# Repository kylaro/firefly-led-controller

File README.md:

# firefly-led-controller
PCB for the FireFly LED Controller by kylarLEDs

https://imgur.com/a/bOtsNqd

## Hardware
    The sensors on the board are:
        1. Microphone  -> for sound reactive LEDs
        2. Potentiometer  -> for brightness control
        3. Rotary encoder  -> for color/hue control
        4. Rotary encoder button  -> for changing patterns

    The outputs from the board are:
        1. 2 x WS2812B LED output pins 
            a. Each pin has 2 output pads, one on front and one on back
            b. Each pin has a 0.1 inch header port
        2. 2 x USBC 5V power up to 3A

    The input to the boards are:
        1. Pico programming micro usb port (not meant for power)
        2. 1 x USBC 5V power up to 3A

## Notes
Necessary improvements:
  * Support for 4 pin ws2812b strips, and APA102, 4 outputs
  * More testing capability for the microphone, and maybe other components
*     -> maybe bottom of board row of headers that another board with a pi can plug into, or row of pads on bottom
*     -> Or pad groups on the bottom, like this to that type things... every connection could be represented
*     -> ex. MIC GND <-> GND ... ENC_A <-> GP22 ..., anything that contributes functionality :) 
  * 4 LED outputs
  * Header pins offset

Possibile Improvements to make:
    *WIRELESS:
    *Add ESP32 S2 ($2) with PCB antenna, may need a 3.3V regulator unless the 3.3V port can handle it
  * Add a power MOSFET to turn on / off the power to LEDs
  * Have power pads for screw down crimped ring terminals?
  * Have a hole on the board to weave the LED wire through to add mechanical stability to solder connections
  * Support for 12V on board? (5v regulator, 5v dataline, but 12v power)
  * Support for automatically detecting strip length based on current drawn by strip (either "off" current or turning 1 on at a time, need ammeter)
  * Support for battery charging
  * Support for DMX LEDs input/output
  * Add more sensors, like motion sensor for human presence detection. Temperature/accelerometer/humidity/gyro...
  * Add silabs MCU for mesh networking
  * Stop using Pico board, use the RP2040 + pico schematic so we aren't soldering a board onto a board!

Notes:
  * USB C holes should be more exact so it fits better

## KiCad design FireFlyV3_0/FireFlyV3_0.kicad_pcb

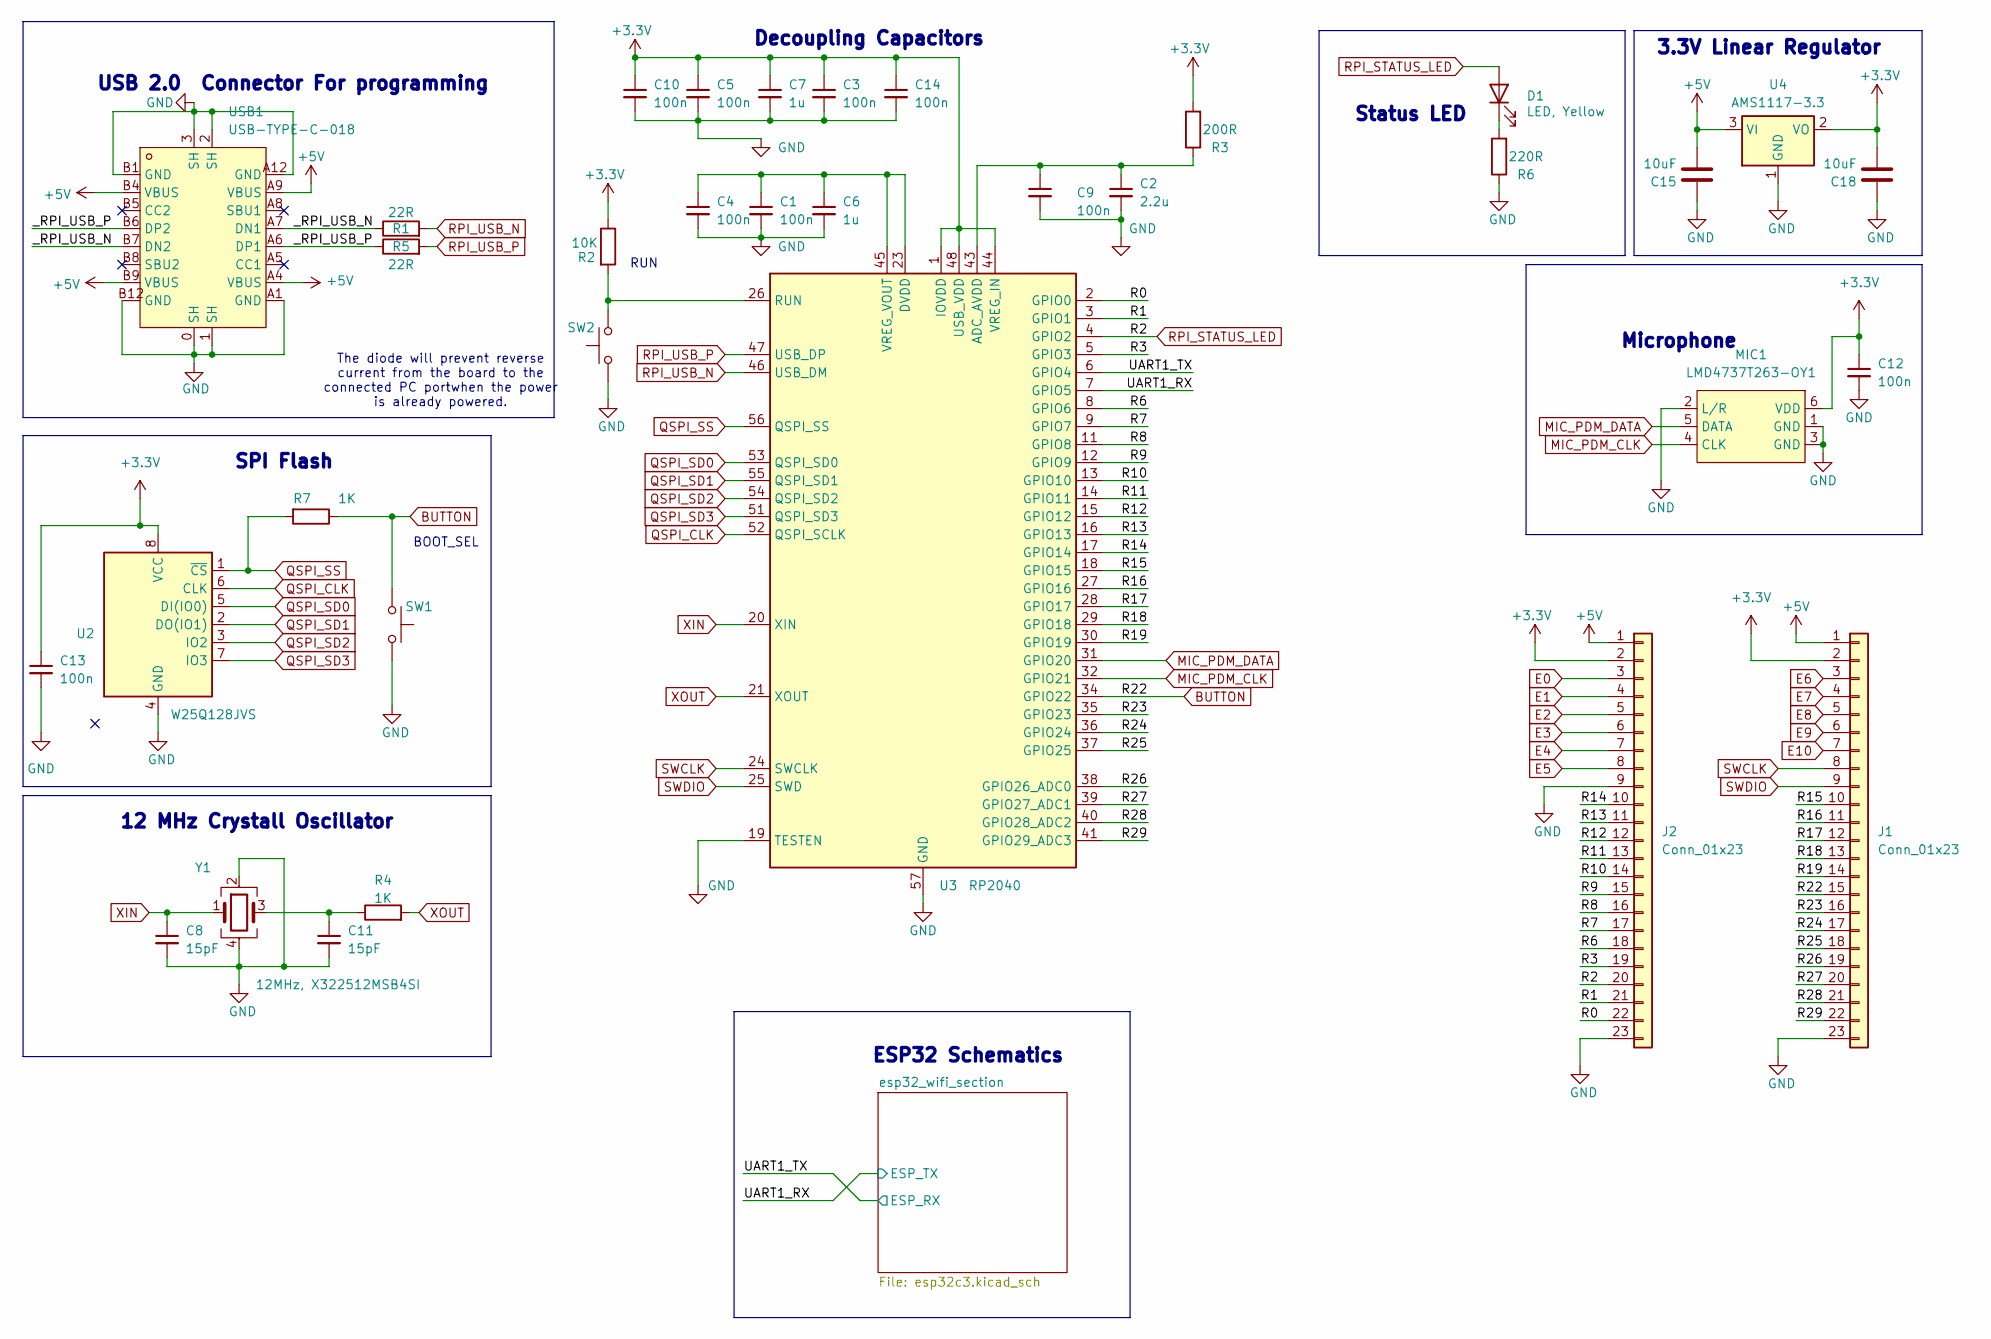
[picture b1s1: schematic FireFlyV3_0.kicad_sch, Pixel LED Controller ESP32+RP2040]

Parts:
C1, C3, C4, C5, C9, C10, C12, C13, C14: 100n; C_0402_1005Metric; LCSC Part C1525
C2: 2.2u; C_0402_1005Metric; LCSC Part C12530
C6, C7: 1u; C_0402_1005Metric; LCSC Part C52923
C8, C11: 15pF; C_0402_1005Metric; LCSC Part C1548
C15, C18: 10uF; C_0603_1608Metric; LCSC Part C19702
D1: LED, Yellow; LED_0603_1608Metric; LCSC Part C72038
J1, J2: Conn_01x23; PinHeader_1x23_P2.54mm_Vertical
MIC1: LMD4737T263-OY1; LGA-6_L4.7-W3.8-P1.65_LMD4737T; LCSC Part C5373239
R1, R5: 22R; R_0402_1005Metric; LCSC Part C25092
R2: 10K; R_0402_1005Metric; LCSC Part C25744
R3: 200R; R_0402_1005Metric; LCSC Part C25087
R4, R7: 1K; R_0402_1005Metric; LCSC Part C11702
R6: 220R; R_0402_1005Metric; LCSC Part C25091
SW1, SW2: BTN; SW_SPST_TL3342; LCSC Part C318884
U2: W25Q128JVS; SOIC-8_5.275x5.275mm_P1.27mm; LCSC Part C97521
U3: RP2040; QFN-56-1EP_7x7mm_P0.4mm_EP3.2x3.2mm; LCSC Part C2040
U4: AMS1117-3.3; SOT-223-3_TabPin2; LCSC Part C6186
USB1: USB-TYPE-C-018; USB-C_SMD-TYPE-C-31-M-12; LCSC Part C2927038
Y1: 12MHz, X322512MSB4SI; Crystal_SMD_3225-4Pin_3.2x2.5mm; LCSC Part C9002

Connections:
+3.3V: C3.1, C5.1, C7.1, C10.1, C12.1, C13.1, C14.1, C18.1, J1.2, J2.2, MIC1.6 (VDD), R2.1, R3.2, U2.8 (VCC), U3.1 (IOVDD), U3.10 (IOVDD), U3.22 (IOVDD), U3.33 (IOVDD), U3.42 (IOVDD), U3.44 (VREG_IN), U3.48 (USB_VDD), U3.49 (IOVDD), U4.2 (VO); also elsewhere on the board
+5V: C15.1, J1.1, J2.1, U4.3 (VI), USB1.A4 (VBUS), USB1.A9 (VBUS), USB1.B4 (VBUS), USB1.B9 (VBUS); also elsewhere on the board
/R0: J2.22, U3.2 (GPIO0)
/R1: J2.21, U3.3 (GPIO1)
/R3: J2.19, U3.5 (GPIO3)
/R6: J2.18, U3.8 (GPIO6)
/R7: J2.17, U3.9 (GPIO7)
/R8: J2.16, U3.11 (GPIO8)
/R9: J2.15, U3.12 (GPIO9)
/R10: J2.14, U3.13 (GPIO10)
/R11: J2.13, U3.14 (GPIO11)
/R12: J2.12, U3.15 (GPIO12)
/R13: J2.11, U3.16 (GPIO13)
/R14: J2.10, U3.17 (GPIO14)
/R15: J1.10, U3.18 (GPIO15)
/R16: J1.11, U3.27 (GPIO16)
/R17: J1.12, U3.28 (GPIO17)
/R18: J1.13, U3.29 (GPIO18)
/R19: J1.14, U3.30 (GPIO19)
/R23: J1.16, U3.35 (GPIO23)
/R24: J1.17, U3.36 (GPIO24)
/R25: J1.18, U3.37 (GPIO25)
/R26: J1.19, U3.38 (GPIO26_ADC0)
/R27: J1.20, U3.39 (GPIO27_ADC1)
/R28: J1.21, U3.40 (GPIO28_ADC2)
/R29: J1.22, U3.41 (GPIO29_ADC3)
/UART1_RX: U3.7 (GPIO5); also elsewhere on the board
/UART1_TX: U3.6 (GPIO4); also elsewhere on the board
/_RPI_USB_N: R1.1, USB1.A7 (DN1), USB1.B7 (DN2)
/_RPI_USB_P: R5.1, USB1.A6 (DP1), USB1.B6 (DP2)
BUTTON: J1.15, R7.1, SW1.1, U3.34 (GPIO22)
E0: J2.3; also elsewhere on the board
E1: J2.4; also elsewhere on the board
E2: J2.5; also elsewhere on the board
E3: J2.6; also elsewhere on the board
E4: J2.7; also elsewhere on the board
E5: J2.8; also elsewhere on the board
E6: J1.3; also elsewhere on the board
E7: J1.4; also elsewhere on the board
E8: J1.5; also elsewhere on the board
E9: J1.6; also elsewhere on the board
E10: J1.7; also elsewhere on the board
GND: C1.2, C2.2, C3.2, C4.2, C5.2, C6.2, C7.2, C8.2, C9.2, C10.2, C11.2, C12.2, C13.2, C14.2, C15.2, C18.2, J1.23, J2.9, J2.23, MIC1.1 (GND), MIC1.2 (L/R), MIC1.3 (GND), R6.1, SW1.2, SW2.2, U2.4 (GND), U3.19 (TESTEN), U3.57 (GND), U4.1 (GND), USB1.0 (SH), USB1.1 (SH), USB1.2 (SH), USB1.3 (SH), USB1.A1 (GND), USB1.A12 (GND), USB1.B1 (GND), USB1.B12 (GND), Y1.2, Y1.4; also elsewhere on the board
MIC_PDM_CLK: MIC1.4 (CLK), U3.32 (GPIO21)
MIC_PDM_DATA: MIC1.5 (DATA), U3.31 (GPIO20)
unnamed: C11.1, R4.1, Y1.3
unnamed: D1.1 (K), R6.2
unnamed: C2.1, C9.1, R3.1, U3.43 (ADC_AVDD)
unnamed: R2.2, SW2.1, U3.26 (RUN)
unnamed: C1.1, C4.1, C6.1, U3.23 (DVDD), U3.45 (VREG_VOUT), U3.50 (DVDD)
QSPI_CLK: U2.6 (CLK), U3.52 (QSPI_SCLK)
QSPI_SD0: U2.5 (DI(IO0)), U3.53 (QSPI_SD0)
QSPI_SD1: U2.2 (DO(IO1)), U3.55 (QSPI_SD1)
QSPI_SD2: U2.3 (IO2), U3.54 (QSPI_SD2)
QSPI_SD3: U2.7 (IO3), U3.51 (QSPI_SD3)
QSPI_SS: R7.2, U2.1 (~CS), U3.56 (QSPI_SS)
RPI_STATUS_LED: D1.2 (A), J2.20, U3.4 (GPIO2)
RPI_USB_N: R1.2, U3.46 (USB_DM)
RPI_USB_P: R5.2, U3.47 (USB_DP)
SWCLK: J1.8, U3.24 (SWCLK)
SWDIO: J1.9, U3.25 (SWD)
XIN: C8.1, U3.20 (XIN), Y1.1
XOUT: R4.2, U3.21 (XOUT)

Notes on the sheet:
3.3V Linear Regulator
Microphone
SPI Flash
Decoupling Capacitors
12 MHz Crystall Oscillator
RUN
The diode will prevent reverse current from the board to the connected PC portwhen the power is already powered.
USB 2.0 Connector For programming
BOOT_SEL
Status LED
ESP32 Schematics

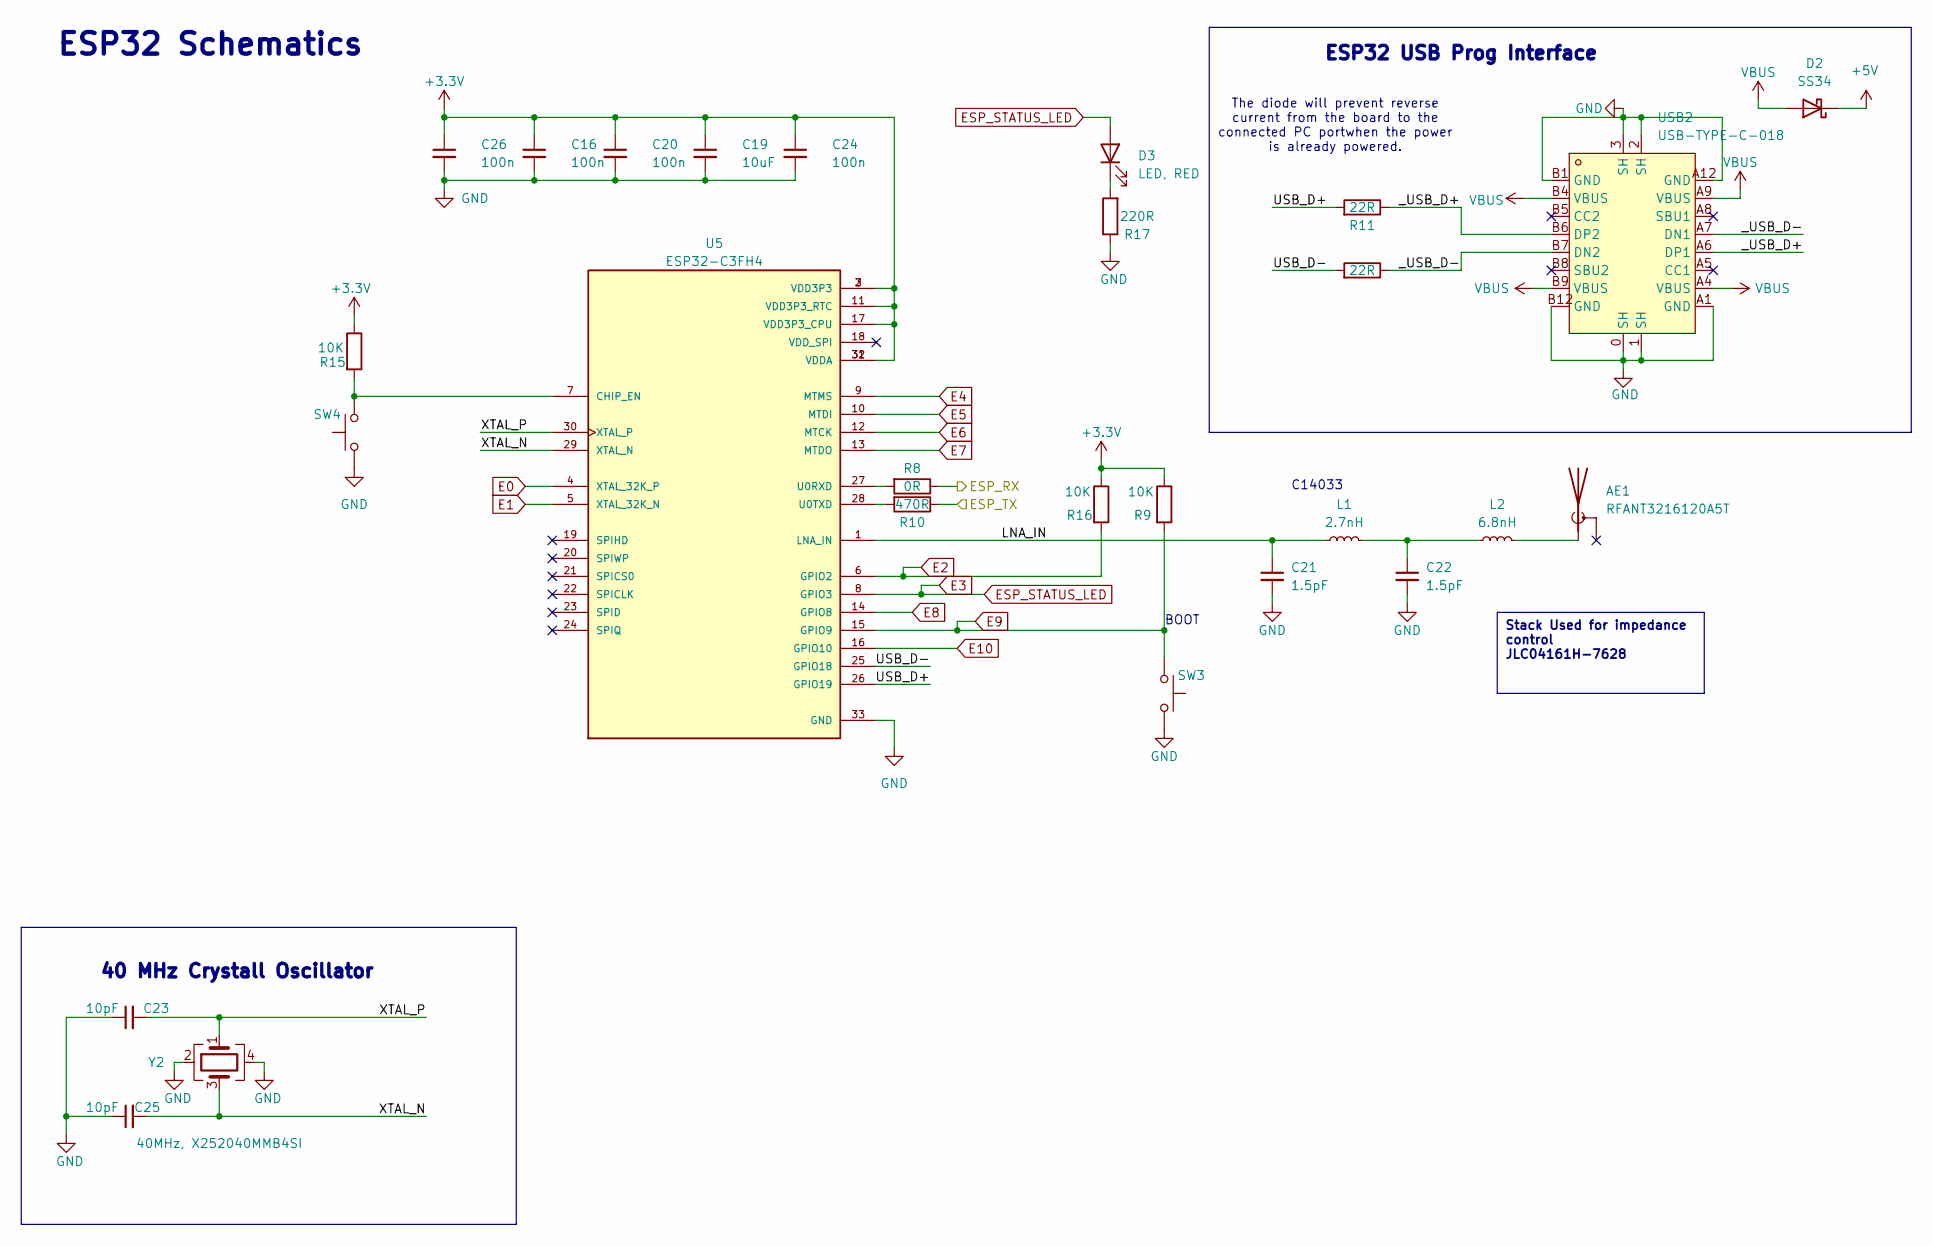
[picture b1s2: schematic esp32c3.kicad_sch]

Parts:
AE1: RFANT3216120A5T; FILTER-SMD_1206-2P-L3.2-W1.6-L; LCSC Part C127629
C16, C20, C24, C26: 100n; C_0402_1005Metric; LCSC Part C1525
C19: 10uF; C_0603_1608Metric; LCSC Part C19702
C21, C22: 1.5pF; C_0402_1005Metric; LCSC Part C1552
C23, C25: 10pF; C_0402_1005Metric; LCSC Part C32949
D2: SS34; D_SMA; LCSC Part C8678
D3: LED, RED; LED_0603_1608Metric; LCSC Part C2286
L1: 2.7nH; L_0402_1005Metric; LCSC Part C98058
L2: 6.8nH; L_0402_1005Metric; LCSC Part C77110
R8: 0R; R_0402_1005Metric; LCSC Part C17168
R9, R15, R16: 10K; R_0402_1005Metric; LCSC Part C25744
R10: 470R; R_0402_1005Metric; LCSC Part C25117
R11, R13: 22R; R_0402_1005Metric; LCSC Part C25092
R17: 220R; R_0402_1005Metric; LCSC Part C25091
SW3, SW4: BTN; SW_SPST_TL3342; LCSC Part C318884
U5: ESP32-C3FH4; MPN ESP32-C3FH4; LCSC Part C2858491
USB2: USB-TYPE-C-018; USB-C_SMD-TYPE-C-31-M-12; LCSC Part C2927038
Y2: 40MHz, X252040MMB4SI; Crystal_SMD_2520-4Pin_2.5x2.0mm; LCSC Part C2885592

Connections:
+3.3V: C16.1, C19.1, C20.1, C24.1, C26.1, R9.1, R15.1, R16.1, U5.2 (VDD3P3), U5.3 (VDD3P3), U5.11 (VDD3P3_RTC), U5.17 (VDD3P3_CPU), U5.31 (VDDA), U5.32 (VDDA); also elsewhere on the board
+5V: D2.1 (K); also elsewhere on the board
/UART1_RX: R10.1; also elsewhere on the board
/UART1_TX: R8.1; also elsewhere on the board
/esp32_wifi_section/LNA_IN: C21.1, L1.1, U5.1 (LNA_IN)
/esp32_wifi_section/USB_D+: R11.2, U5.26 (GPIO19)
/esp32_wifi_section/USB_D-: R13.2, U5.25 (GPIO18)
/esp32_wifi_section/XTAL_N: C25.2, U5.29 (XTAL_N), Y2.3
/esp32_wifi_section/XTAL_P: C23.2, U5.30 (XTAL_P), Y2.1
/esp32_wifi_section/_USB_D+: R11.1, USB2.A6 (DP1), USB2.B6 (DP2)
/esp32_wifi_section/_USB_D-: R13.1, USB2.A7 (DN1), USB2.B7 (DN2)
E0: U5.4 (XTAL_32K_P); also elsewhere on the board
E1: U5.5 (XTAL_32K_N); also elsewhere on the board
E2: R16.2, U5.6 (GPIO2); also elsewhere on the board
E3: D3.2 (A), U5.8 (GPIO3); also elsewhere on the board
E4: U5.9 (MTMS); also elsewhere on the board
E5: U5.10 (MTDI); also elsewhere on the board
E6: U5.12 (MTCK); also elsewhere on the board
E7: U5.13 (MTDO); also elsewhere on the board
E8: U5.14 (GPIO8); also elsewhere on the board
E9: R9.2, SW3.1, U5.15 (GPIO9); also elsewhere on the board
E10: U5.16 (GPIO10); also elsewhere on the board
GND: C16.2, C19.2, C20.2, C21.2, C22.2, C23.1, C24.2, C25.1, C26.2, R17.1, SW3.2, SW4.2, U5.33 (GND), USB2.0 (SH), USB2.1 (SH), USB2.2 (SH), USB2.3 (SH), USB2.A1 (GND), USB2.A12 (GND), USB2.B1 (GND), USB2.B12 (GND), Y2.2, Y2.4; also elsewhere on the board
unnamed: AE1.1 (A), L2.2
unnamed: C22.1, L1.2, L2.1
unnamed: D3.1 (K), R17.2
unnamed: R15.2, SW4.1, U5.7 (CHIP_EN)
unnamed: R8.2, U5.27 (U0RXD)
unnamed: R10.2, U5.28 (U0TXD)
VBUS: D2.2 (A), USB2.A4 (VBUS), USB2.A9 (VBUS), USB2.B4 (VBUS), USB2.B9 (VBUS)

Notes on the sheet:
Stack Used for impedance control JLC04161H-7628
40 MHz Crystall Oscillator
The diode will prevent reverse current from the board to the connected PC portwhen the power is already powered.
ESP32 Schematics
C14033
ESP32 USB Prog Interface
BOOT

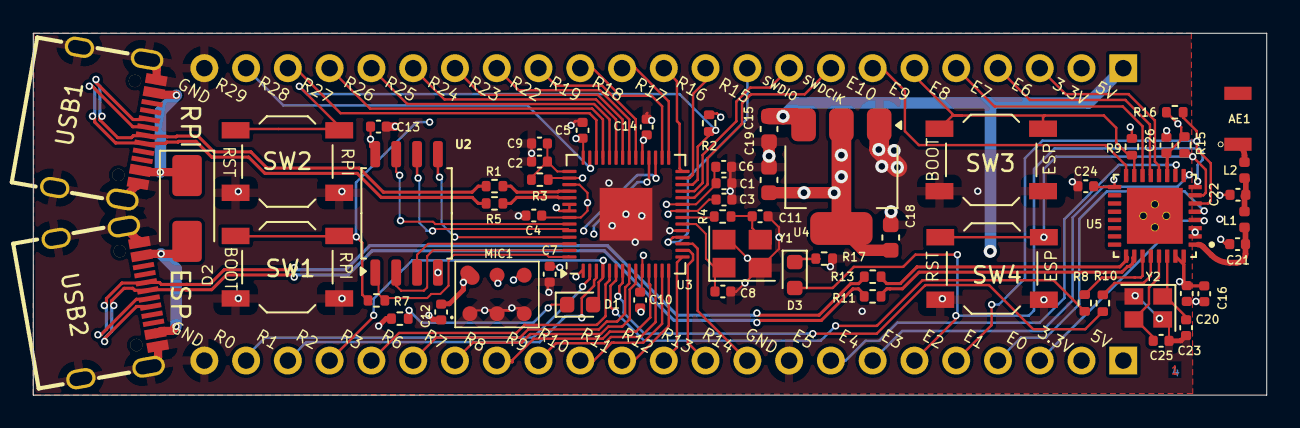
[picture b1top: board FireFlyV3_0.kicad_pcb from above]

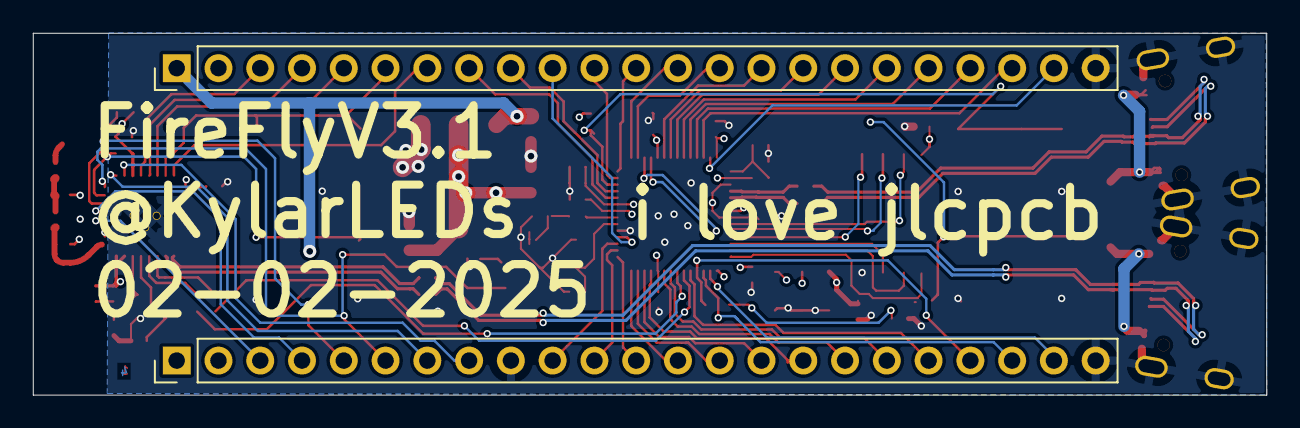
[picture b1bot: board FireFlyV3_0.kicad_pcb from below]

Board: 4 copper layers, 75.0 x 22.0 mm, 61 parts (2 on the bottom side), 77 nets.

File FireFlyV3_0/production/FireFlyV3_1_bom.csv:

Designator,Footprint,Quantity,Value,LCSC Part #
AE1,FILTER-SMD_1206-2P-L3.2-W1.6-L,1,RFANT3216120A5T,C127629
"C1, C10, C12, C13, C14, C16, C20, C24, C26, C3, C4, C5, C9",0402,13,100n,C1525
"C11, C8",0402,2,15pF,C1548
"C15, C18, C19",0603,3,10uF,C19702
C2,0402,1,2.2u,C12530
"C21, C22",0402,2,1.5pF,C1552
"C23, C25",0402,2,10pF,C32949 
"C6, C7",0402,2,1u,C52923
D1,0603,1,"LED, Yellow",C72038
D2,D_SMA,1,SS34,C8678
D3,0603,1,"LED, RED",C2286
"J1, J2",PinHeader_1x23_P2.54mm_Vertical,2,Conn_01x23,
L1,0402,1,2.7nH, C98058
L2,0402,1,6.8nH,C77110
MIC1,LGA-6_L4.7-W3.8-P1.65_LMD4737T,1,LMD4737T263-OY1,C5373239
"R1, R11, R13, R5",0402,4,22R,C25092
R10,0402,1,470R,C25117 
"R15, R16, R2, R9",0402,4,10K,C25744
"R17, R6",0402,2,220R,C25091
R3,0402,1,200R,C25087
"R4, R7",0402,2,1K,C11702
R8,0402,1,0R,C17168 
"SW1, SW2, SW3, SW4",SW_SPST_TL3342,4,BTN,C318884
U2,SOIC-8_5.275x5.275mm_P1.27mm,1,W25Q128JVS, C97521
U3,QFN-56-1EP_7x7mm_P0.4mm_EP3.2x3.2mm,1,RP2040,C2040
U4,SOT-223-3_TabPin2,1,AMS1117-3.3,C6186
U5,ESP32-C3FH4,1,ESP32-C3FH4,C2858491
"USB1, USB2",USB-C_SMD-TYPE-C-31-M-12,2,USB-TYPE-C-018,C2927038
Y1,Crystal_SMD_3225-4Pin_3.2x2.5mm,1,"12MHz, X322512MSB4SI",C9002
Y2,Crystal_SMD_2520-4Pin_2.5x2.0mm,1,"40MHz, X252040MMB4SI",C2885592

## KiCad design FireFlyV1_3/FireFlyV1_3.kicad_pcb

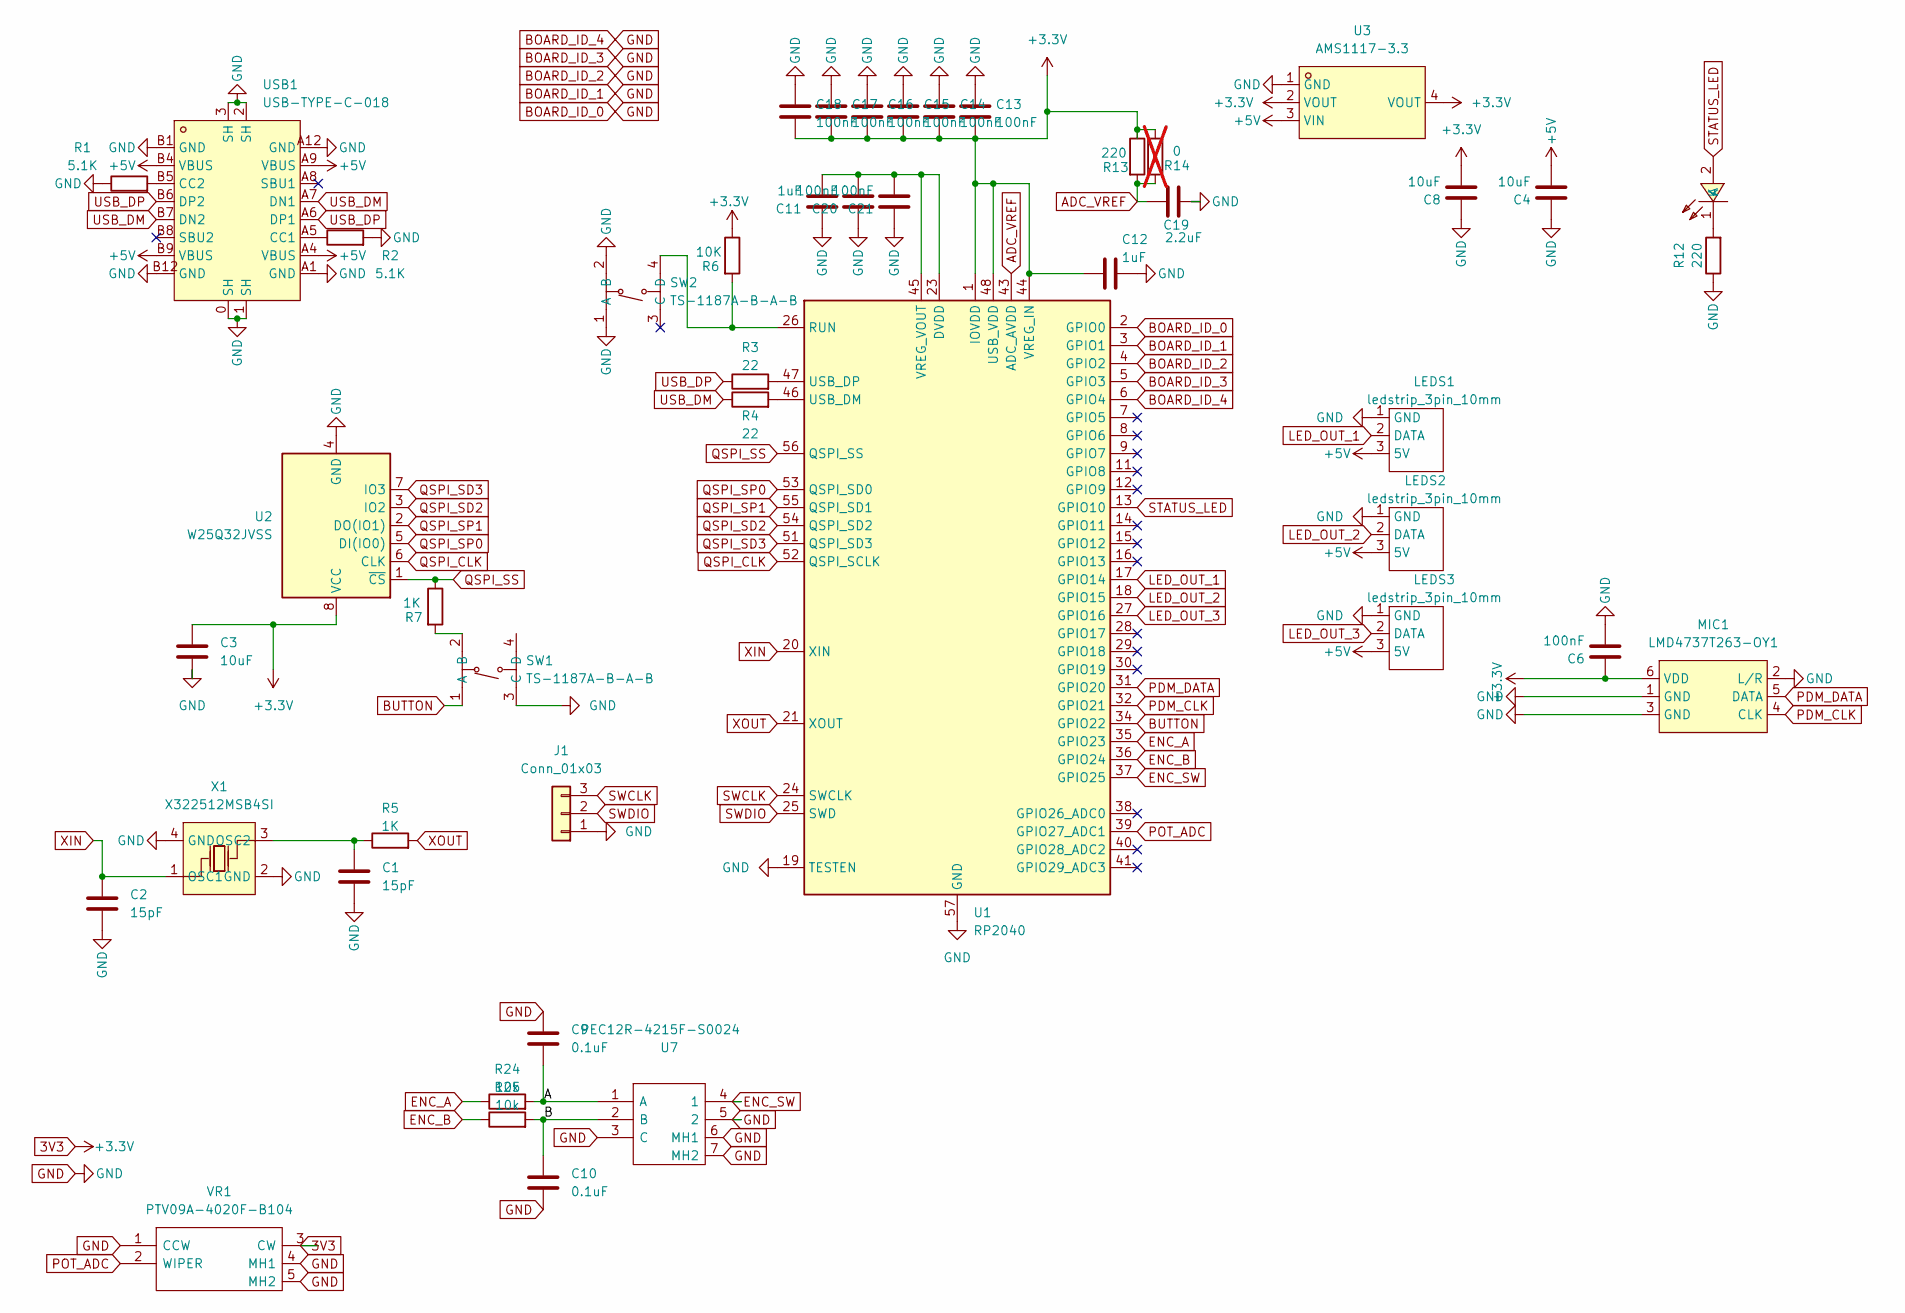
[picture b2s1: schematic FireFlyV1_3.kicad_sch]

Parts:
C1, C2: 15pF; C_0402_1005Metric
C3, C4, C8: 10uF; C_0402_1005Metric
C6, C13, C14, C15, C16, C17, C18, C20, C21: 100nF; C_0402_1005Metric
C9, C10: 0.1uF; C_0402_1005Metric
C11, C12: 1uF; C_0402_1005Metric
C19: 2.2uF; C_0402_1005Metric
J1: Conn_01x03; PinHeader_1x03_P2.54mm_Vertical
LED1: KT-0603R; LED0603-RD; LCSC Part C2286
LEDS1, LEDS2, LEDS3: ledstrip_3pin_10mm; ledstrip_3pin_withpins
MIC1: LMD4737T263-OY1; LGA-6_L4.7-W3.8-P1.65_LMD4737T; LCSC Part C5373239
R1, R2: 5.1K; R_0402_1005Metric
R3, R4: 22; R_0402_1005Metric
R5, R7: 1K; R_0402_1005Metric
R6: 10K; R_0402_1005Metric
R12, R13: 220; R_0402_1005Metric
R14: 0; R_0402_1005Metric; not fitted
R24, R25: 10k; R_0402_1005Metric
SW1, SW2: TS-1187A-B-A-B; SW-SMD_4P-L5.1-W5.1-P3.70-LS6.5-TL-2; LCSC Part C318884
U1: RP2040; QFN-56-1EP_7x7mm_P0.4mm_EP3.2x3.2mm
U2: W25Q32JVSS; SOIC-8_5.23x5.23mm_P1.27mm
U3: AMS1117-3.3; SOT-223-3_L6.5-W3.4-P2.30-LS7.0-BR; LCSC Part C6186
U7: PEC12R-4215F-S0024; PEC12R-4XXXF-SXXXX_court; Mouser Part Number 652-PEC12R-4215F-S24
USB1: USB-TYPE-C-018; USB-C_SMD-TYPE-C-31-M-12; LCSC Part C2927038
VR1: PTV09A-4020F-B104; PTV09A4020FB103; Mouser Part Number 652-PTV09A-4020FB104
X1: X322512MSB4SI; OSC-SMD_4P-L3.2-W2.5-BL; LCSC Part C9002

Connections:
3V3: C3.2, C6.2, C8.1, C12.1, C13.1, C14.1, C15.1, C16.1, C17.1, C18.1, MIC1.6 (VDD), R6.1, R13.1, R14.1, U1.1 (IOVDD), U1.10 (IOVDD), U1.22 (IOVDD), U1.33 (IOVDD), U1.42 (IOVDD), U1.44 (VREG_IN), U1.48 (USB_VDD), U1.49 (IOVDD), U2.8 (VCC), U3.2 (VOUT), U3.4 (VOUT), VR1.3 (CW)
+5V: C4.1, LEDS1.3 (5V), LEDS2.3 (5V), LEDS3.3 (5V), U3.3 (VIN), USB1.A4 (VBUS), USB1.A9 (VBUS), USB1.B4 (VBUS), USB1.B9 (VBUS)
/A: C9.1, R24.2, U7.1 (A)
/B: C10.2, R25.2, U7.2 (B)
ADC_VREF: C19.1, R13.2, R14.2, U1.43 (ADC_AVDD)
BOARD_ID_0: C1.1, C2.1, C3.1, C4.2, C6.1, C8.2, C9.2, C10.1, C11.2, C12.2, C13.2, C14.2, C15.2, C16.2, C17.2, C18.2, C19.2, C20.2, C21.2, J1.1, LEDS1.1 (GND), LEDS2.1 (GND), LEDS3.1 (GND), MIC1.1 (GND), MIC1.2 (L/R), MIC1.3 (GND), R1.1, R2.2, R12.1, SW1.3 (C), SW2.1 (A), SW2.2 (B), U1.2 (GPIO0), U1.3 (GPIO1), U1.4 (GPIO2), U1.5 (GPIO3), U1.6 (GPIO4), U1.19 (TESTEN), U1.57 (GND), U2.4 (GND), U3.1 (GND), U7.3 (C), U7.5 (2), U7.6 (MH1), U7.7 (MH2), USB1.0 (SH), USB1.1 (SH), USB1.2 (SH), USB1.3 (SH), USB1.A1 (GND), USB1.A12 (GND), USB1.B1 (GND), USB1.B12 (GND), VR1.1 (CCW), VR1.4 (MH1), VR1.5 (MH2), X1.2 (GND), X1.4 (GND)
BUTTON: SW1.1 (A), U1.34 (GPIO22)
ENC_A: R24.1, U1.35 (GPIO23)
ENC_B: R25.1, U1.36 (GPIO24)
ENC_SW: U1.37 (GPIO25), U7.4 (1)
LED_OUT_1: LEDS1.2 (DATA), U1.17 (GPIO14)
LED_OUT_2: LEDS2.2 (DATA), U1.18 (GPIO15)
LED_OUT_3: LEDS3.2 (DATA), U1.27 (GPIO16)
unnamed: LED1.1 (K), R12.2
unnamed: R7.2, SW1.2 (B)
unnamed: R6.2, SW2.4 (D), U1.26 (RUN)
unnamed: R4.2, U1.46 (USB_DM)
unnamed: R3.2, U1.47 (USB_DP)
unnamed: C11.1, C20.1, C21.1, U1.23 (DVDD), U1.45 (VREG_VOUT), U1.50 (DVDD)
unnamed: R2.1, USB1.A5 (CC1)
unnamed: R1.2, USB1.B5 (CC2)
unnamed: C1.2, R5.1, X1.3 (OSC2)
PDM_CLK: MIC1.4 (CLK), U1.32 (GPIO21)
PDM_DATA: MIC1.5 (DATA), U1.31 (GPIO20)
POT_ADC: U1.39 (GPIO27_ADC1), VR1.2 (WIPER)
QSPI_CLK: U1.52 (QSPI_SCLK), U2.6 (CLK)
QSPI_SD2: U1.54 (QSPI_SD2), U2.3 (IO2)
QSPI_SD3: U1.51 (QSPI_SD3), U2.7 (IO3)
QSPI_SP0: U1.53 (QSPI_SD0), U2.5 (DI(IO0))
QSPI_SP1: U1.55 (QSPI_SD1), U2.2 (DO(IO1))
QSPI_SS: R7.1, U1.56 (QSPI_SS), U2.1 (~CS)
STATUS_LED: LED1.2 (A), U1.13 (GPIO10)
SWCLK: J1.3, U1.24 (SWCLK)
SWDIO: J1.2, U1.25 (SWD)
USB_DM: R4.1, USB1.A7 (DN1), USB1.B7 (DN2)
USB_DP: R3.1, USB1.A6 (DP1), USB1.B6 (DP2)
XIN: C2.2, U1.20 (XIN), X1.1 (OSC1)
XOUT: R5.2, U1.21 (XOUT)

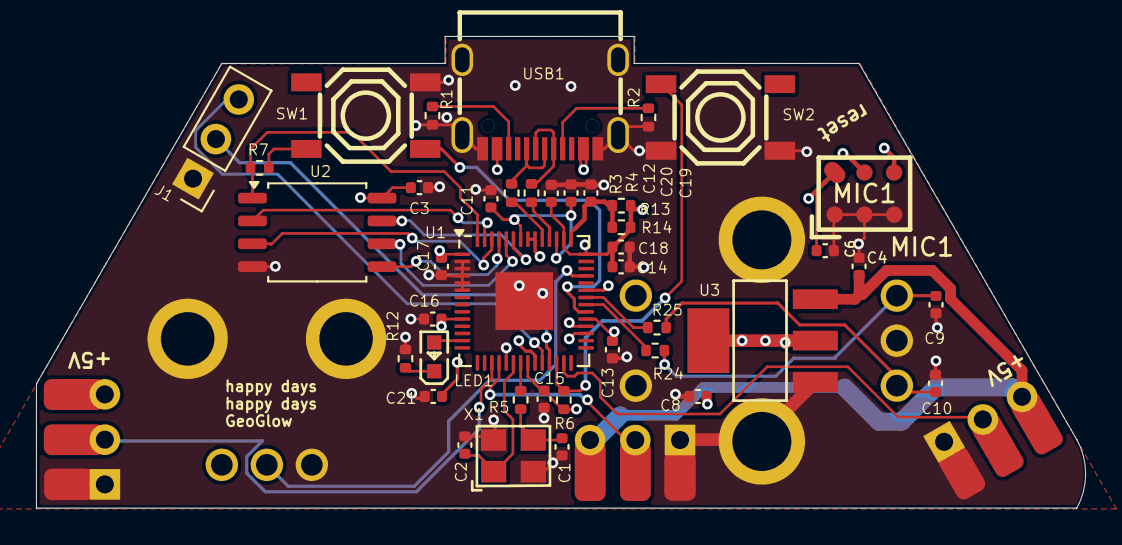
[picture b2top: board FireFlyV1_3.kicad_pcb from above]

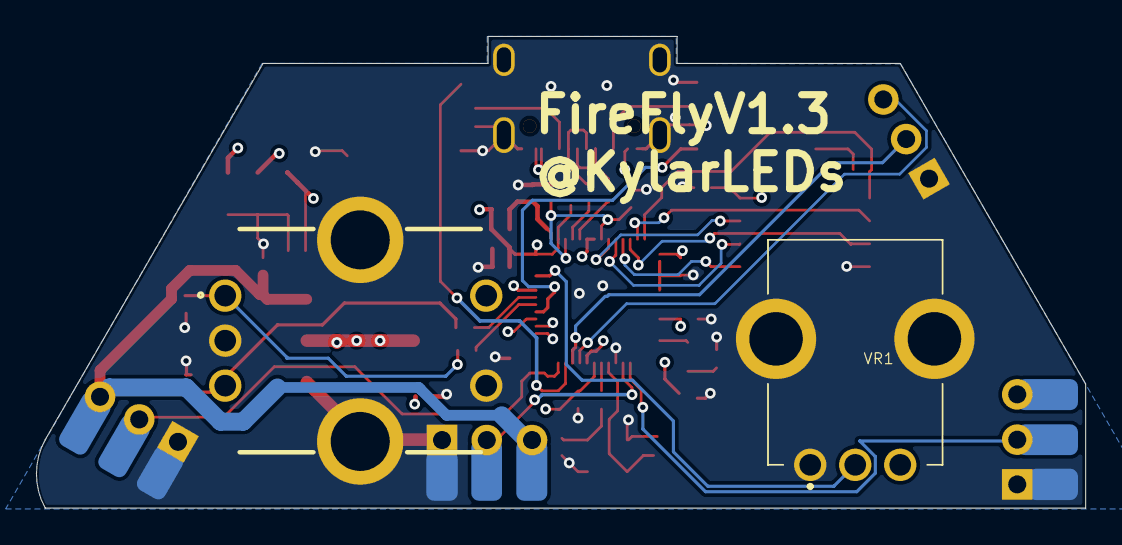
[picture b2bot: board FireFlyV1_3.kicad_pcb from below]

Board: 4 copper layers, 58.3 x 26.2 mm, 46 parts (4 on the bottom side), 38 nets.

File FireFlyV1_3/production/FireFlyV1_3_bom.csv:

Designator,Footprint,Quantity,Value,LCSC Part #
"C1, C2",0402,2,15pF,
"C10, C9",0402,2,0.1uF,
"C11, C12",0402,2,1uF,
"C13, C14, C15, C16, C17, C18, C20, C21, C6",0402,9,100nF,
C19,0402,1,2.2uF,
"C3, C4, C8",0402,3,10uF,
J1,PinHeader_1x03_P2.54mm_Vertical,1,Conn_01x03,
LED1,LED0603-RD,1,KT-0603R,C2286
"LEDS1, LEDS2, LEDS3",ledstrip_3pin_withpins,3,ledstrip_3pin_10mm,
MIC1,LGA-6_L4.7-W3.8-P1.65_LMD4737T,1,LMD4737T263-OY1,C5373239
"R1, R2",0402,2,5.1K,
"R12, R13",0402,2,220,
"R24, R25, R6",0402,3,10k,
"R3, R4",0402,2,22,
"R5, R7",0402,2,1K,
"SW1, SW2",SW-SMD_4P-L5.1-W5.1-P3.70-LS6.5-TL-2,2,TS-1187A-B-A-B,C318884
U1,QFN-56-1EP_7x7mm_P0.4mm_EP3.2x3.2mm,1,RP2040,
U2,SOIC-8_5.23x5.23mm_P1.27mm,1,W25Q32JVSS,
U3,SOT-223-3_L6.5-W3.4-P2.30-LS7.0-BR,1,AMS1117-3.3,C6186
USB1,USB-C_SMD-TYPE-C-31-M-12,1,USB-TYPE-C-018,C2927038
X1,OSC-SMD_4P-L3.2-W2.5-BL,1,X322512MSB4SI,C9002
